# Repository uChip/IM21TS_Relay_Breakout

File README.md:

# IM21TS Relay Breakout PCB  

Eagle CAD PCB design for a breakout board.  
Converts TE Connectivity's IM21TS relay to 0.1" breadboard format.  

## Component Description  

IM21TS Relay:  
  * Non-Latching, DPDT  
  * Coil Voltage - 3VDC  
  * Coil Current - 16.7mA  
  * Switch Voltage - 250VAC  
  * Contact Rating - 2A  

Digi-Key part #PB1167-ND  

Pinout on PCB or see datasheet.  

## Order PCBs

You can order this PCB from OSH Park.  The link below will take you to the appropriate page of the OSH park website.  
  * http://www.oshpark.com/shared_projects/KSq63Xbr

## File Formats  

Files are in "CadSoft EAGLE PCB Design Software" .brd and .sch formats.  
A free version of the software can be downloaded from www.cadsoftusa.com.  

## Distribution License  

This PCB design is Public Domain. No liability accepted.

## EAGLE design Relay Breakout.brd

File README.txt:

## IM21TS Relay Breakout PCB

Breakout board for TE Connectivity's IM21TS relay.  Converts to 0.1" breadboard format.

### Component Description

IM21TS Relay:
    Non-Latching, DPDT
    Coil Voltage - 3VDC
    Coil Current - 16.7mA
    Switch Voltage - 250VAC
    Contact Rating - 2A

Digi-Key part #PB1167-ND

Pinout on PCB or see datasheet.

Distribution License: Public Domain

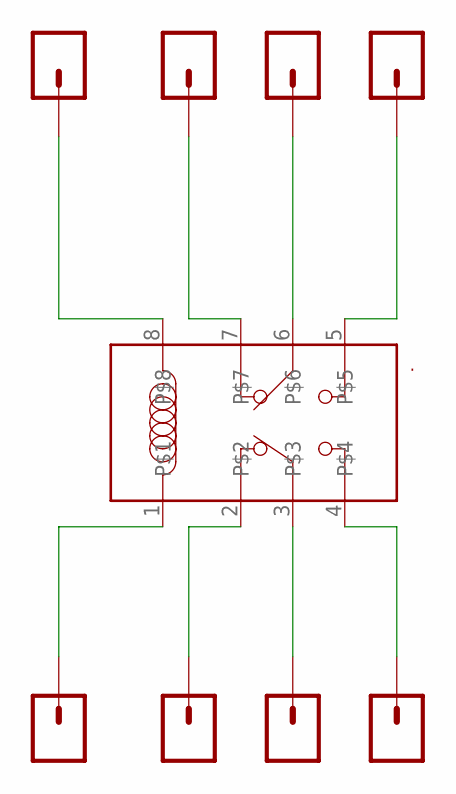
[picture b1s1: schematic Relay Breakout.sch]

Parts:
.: IM21IM21-THT; THT
JP3, JP4, JP5, JP6, JP7, JP8, JP9, JP10: M01PTH; 1X01

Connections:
unnamed: ..8, JP10.1
unnamed: ..7, JP9.1
unnamed: ..6, JP8.1
unnamed: ..5, JP7.1
unnamed: ..4, JP6.1
unnamed: ..3, JP5.1
unnamed: ..2, JP4.1
unnamed: ..1, JP3.1

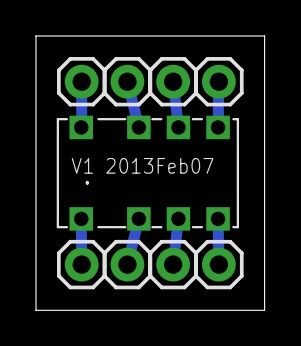
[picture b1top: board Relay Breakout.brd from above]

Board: 2 copper layers, 12.7 x 15.2 mm, 9 parts (0 on the bottom side), 8 nets.

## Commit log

2013-06-19 First commit but of finished design
    Pushing this design to GitHub for distribution and collaboration. NOTE:
    README is placeholder borrowed from another project. Need to rewrite it
    to address this board.
2013-06-19 Changes to README
2013-06-19 Edits to README
2013-06-19 Still trying to get GitHub to recognize README file.
2013-06-19 Adding PCB renderings copied from OSHPark.com
2013-09-29 Worked on README formatting
2013-10-15 Updating .gitignore to ignore Eagle backup files
2013-10-17 Fiddling with README
    Added liability disclaimer. Added link to OSH Park sharing. Changed
    formatting.

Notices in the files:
parts and their libraries:
SparkFun-Connectors: Licensing: CC v3.0 Share-Alike You are welcome to use this library for commercial purposes.
